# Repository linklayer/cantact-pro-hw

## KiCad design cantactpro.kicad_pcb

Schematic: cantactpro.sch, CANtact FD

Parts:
C1, C2: 4.7u; C_0805; MPN CL21A475KAQNNNG
C3: 10u; C_0805; MPN CL21A106KPFNNNG
C4, C7, C11: 0.1u; C_0603; MPN CC0603ZRY5V9BB104
C5, C6: 470 pF/5 kV; C_1812; MPN 202S43W471KV4E
C8, C9: 0.1u; C_0603; MPN CL10F104ZO8NNNC
C10, C12: 100p; C_0603; MPN 885012206077
D1, D3: LED_GRN; LED_0603; MPN LTST-S270KGKT
D2, D4: LED_RED; LED_0603; MPN LTST-S270KRKT
D5: ESD9X5; SOD-923; MPN ESD9X5.0ST5G
D6: D; D_SMA; MPN S1G
H1, H2, H3, H4: MOUNT_HOLE; MountingHole_3.2mm_M3
J1: USB_B; MPN USB-B1HSB6
J2, J3: DB9; LD09P; MPN LD09P13A4GX00LF
JP1: Boot Switch; TE_1825027-5; MPN 1825027-5
L1: 4.7u; L_0805; MPN LQM21PN4R7NGRD
L2: 47u; L_1206; MPN LB3218T470K
LP1, LP2, LP3, LP4: Light Pipe; SLP3-150-zzz-x; MPN SLP3-150-100-F
R1, R2, R3, R4, R5, R6, R7: 100; R_0603; MPN ESR03EZPJ102
R8: 10k; R_0603; MPN RC0603JR-0710KL
R9, R10: 2.7k; R_0603; MPN RMCF0603JT2K70
R11: 1k; R_0603; MPN RC0603JR-071KL
TP1, TP2, TP3, TP4, TP5, TP6, TP7, TP8, TP9, TP10, TP11, TP12, TP13, TP14, TP15, TP16: TEST; Measurement_Point_Round-TH_Small
U1: TPD2E2U06; SOT-553; MPN TPD2E2U06DRLR
U2: AP2114H-3.3; SOT-223; MPN AP2114H-3.3TRG1
U3: ROE-0505S; MPN ROE-0505S
U4: Si864x; SOIC-16_3.9x9.9mm_Pitch1.27mm; MPN SI8642AB-B-IS1R
U5: LTV-846; SMD-16; MPN LTV-846S
U6, U11: 74LVC1G3157; SOT-363_SC-70-6; MPN SN74LVC1G3157DCKR
U7: NCV7356D1; SOIC-8_3.9x4.9mm_Pitch1.27mm; MPN NCV7356D1R2G
U8: MCP25612FD; SOIC-14_3.9x8.7mm_Pitch1.27mm; MPN MCP25612FD-H/SL
U9, U10: NUP2125; SC-70; MPN NUP2125WTT1G

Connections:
+3V3: C2.1, C4.1, TP3.1, U2.2, U2.4, U4.1, U4.7, U5.3, U5.5, U5.7; also elsewhere on the board
+5VD: C5.1, C7.2, C8.1, C9.1, R9.1, TP9.1, U3.4, U4.10, U4.16, U5.10, U5.12, U5.14, U6.5, U8.3, U8.7, U11.5
+12V: C10.1, C11.2, D6.1 (K), U7.5
/12V_DB9: D6.2 (A), J2.9
/CAN0_MODE: R8.2, TP14.1, U5.9, U6.6, U11.6
/CAN0_RX: TP12.1, U4.12, U11.4
/CAN0_RX_HS: U8.4, U11.3
/CAN0_RX_SW: R9.2, U7.4, U11.1
/CAN0_TX: TP10.1, U4.14, U6.4
/CAN0_TX_HS: U6.3, U8.1
/CAN0_TX_SW: U6.1, U7.1
/CAN1_RX: TP13.1, U4.11, U8.8
/CAN1_TX: TP11.1, U4.13, U8.5
/CANH0: J2.7, U8.13, U10.1
/CANH1: J3.7, U8.10, U9.1
/CANH_SW: C12.2, D5.1 (A1), J2.4, L2.2, R11.1
/CANL0: J2.2, U8.12, U10.2
/CANL1: J3.2, U8.9, U9.2
/MCU/BOOTMODE: JP1.1; also elsewhere on the board
/MCU/CAN0_RX: TP6.1, U4.5; also elsewhere on the board
/MCU/CAN0_TX: TP4.1, U4.3; also elsewhere on the board
/MCU/CAN1_RX: TP7.1, U4.6; also elsewhere on the board
/MCU/CAN1_TX: TP5.1, U4.4; also elsewhere on the board
/MCU/LED_1: D1.2 (A); also elsewhere on the board
/MCU/LED_2: D2.2 (A); also elsewhere on the board
/MCU/LED_3: D3.2 (A); also elsewhere on the board
/MCU/LED_4: D4.2 (A); also elsewhere on the board
/MCU/SWCAN_ENABLE: R7.1; also elsewhere on the board
/MCU/SWCAN_MODE0: R5.1; also elsewhere on the board
/MCU/SWCAN_MODE1: R6.1; also elsewhere on the board
/MCU/USB+: J1.3 (D+), U1.5; also elsewhere on the board
/MCU/USB-: J1.2 (D-), U1.3; also elsewhere on the board
/SW_MODE0: TP15.1, U5.13, U7.2
/SW_MODE1: TP16.1, U5.11, U7.3
GND: C1.2, C2.2, C3.2, C4.2, C6.2, J1.4 (GND), J1.5 (Shield), JP1.2, R1.1, R2.1, R3.1, R4.1, TP2.1, U1.4, U2.1, U3.1, U4.2, U4.8; also elsewhere on the board
GNDD: C6.1, C7.1, C8.2, C9.2, C10.2, C11.1, C12.1, D5.2 (A2), J2.3, J2.6, J3.3, J3.6, R8.1, TP8.1, U3.3, U4.9, U4.15, U6.2, U7.8, U8.2, U8.6, U8.11, U8.14, U9.3, U10.3, U11.2
unnamed: C5.2, L1.2, U3.2
unnamed: D1.1 (K), R1.2
unnamed: D2.1 (K), R2.2
unnamed: D3.1 (K), R3.2
unnamed: D4.1 (K), R4.2
unnamed: L2.1, R10.1, R11.2, U7.7
unnamed: R5.2, U5.4
unnamed: R6.2, U5.6
unnamed: R7.2, U5.8
unnamed: R10.2, U7.6
VBUS: C1.1, C3.1, J1.1 (VBUS), L1.1, TP1.1, U2.3; also elsewhere on the board

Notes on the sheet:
Isolation Barrier
Mounting Holes
Light Pipes

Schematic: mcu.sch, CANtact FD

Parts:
C13, C15, C17, C19, C21, C23, C25, C27, C29: 0.01u; C_0603; MPN C0603C103M5RACTU
C14, C16, C18, C20, C22, C24, C26, C28, C32: 0.1u; C_0603; MPN CL10F104ZO8NNNC
C30, C31: 33p; C_0603; MPN CL10C330JB8NNNC
C33: 4.7u; C_0805; MPN CL21A475KAQNNNG
C34: 10u; C_0805; MPN CL21A106KPFNNNG
J4: SWD; Pin_Header_Straight_2x05_Pitch1.27mm; MPN 3220-10-0100-00
R12: 0; R_0603; MPN RC0603JR-070RL
R13: 12.4k; R_0603; MPN ERJ-3EKF1242V
R14, R15: 10k; R_0603; MPN RC0603JR-0710KL
U12: LPC54616J512BD100; LQFP-100_14x14mm_Pitch0.5mm; MPN LPC54616J512BD100E
Y1: 12 MHz; CSM-3X; MPN ECS-120-20-3X-TR

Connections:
+3V3: C13.1, C14.1, C15.1, C16.1, C17.1, C18.1, C19.1, C20.1, C21.1, C22.1, C23.1, C24.1, C25.1, C26.1, C27.1, C28.1, C29.1, C32.1, C33.1, C34.1, J4.1, R14.2, R15.2, U12.1, U12.10, U12.11, U12.21, U12.31, U12.32, U12.33, U12.45, U12.50, U12.54, U12.75, U12.76, U12.99; also elsewhere on the board
/MCU/BOOTMODE: R12.2, U12.90; also elsewhere on the board
/MCU/CAN0_RX: U12.60; also elsewhere on the board
/MCU/CAN0_TX: U12.58; also elsewhere on the board
/MCU/CAN1_RX: U12.5; also elsewhere on the board
/MCU/CAN1_TX: U12.47; also elsewhere on the board
/MCU/ISP0: U12.87
/MCU/ISP1: R12.1, U12.89
/MCU/LED_1: U12.35; also elsewhere on the board
/MCU/LED_2: U12.36; also elsewhere on the board
/MCU/LED_3: U12.37; also elsewhere on the board
/MCU/LED_4: U12.38; also elsewhere on the board
/MCU/RESETN: J4.10, U12.48
/MCU/SWCAN_ENABLE: U12.77; also elsewhere on the board
/MCU/SWCAN_MODE0: U12.83; also elsewhere on the board
/MCU/SWCAN_MODE1: U12.78; also elsewhere on the board
/MCU/SWCLK: J4.4, R15.1, U12.24
/MCU/SWDIO: J4.2, R14.1, U12.25
/MCU/USB+: U12.13; also elsewhere on the board
/MCU/USB-: U12.12; also elsewhere on the board
GND: C13.2, C14.2, C15.2, C16.2, C17.2, C18.2, C19.2, C20.2, C21.2, C22.2, C23.2, C24.2, C25.2, C26.2, C27.2, C28.2, C29.2, C30.1, C31.1, C32.2, C33.2, C34.2, J4.3, J4.5, J4.9, R13.1, U12.2, U12.6, U12.14, U12.22, U12.30, U12.34, U12.49, U12.51, U12.53, U12.71, U12.79, U12.96; also elsewhere on the board
unnamed: C30.2, U12.20, Y1.2
unnamed: C31.2, U12.19, Y1.1
unnamed: R13.2, U12.7
VBUS: U12.9; also elsewhere on the board

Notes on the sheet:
SWD Debug Interface
DNP R14 for MSC Populate for DFU
TODO: CHECK LOAD CAPS

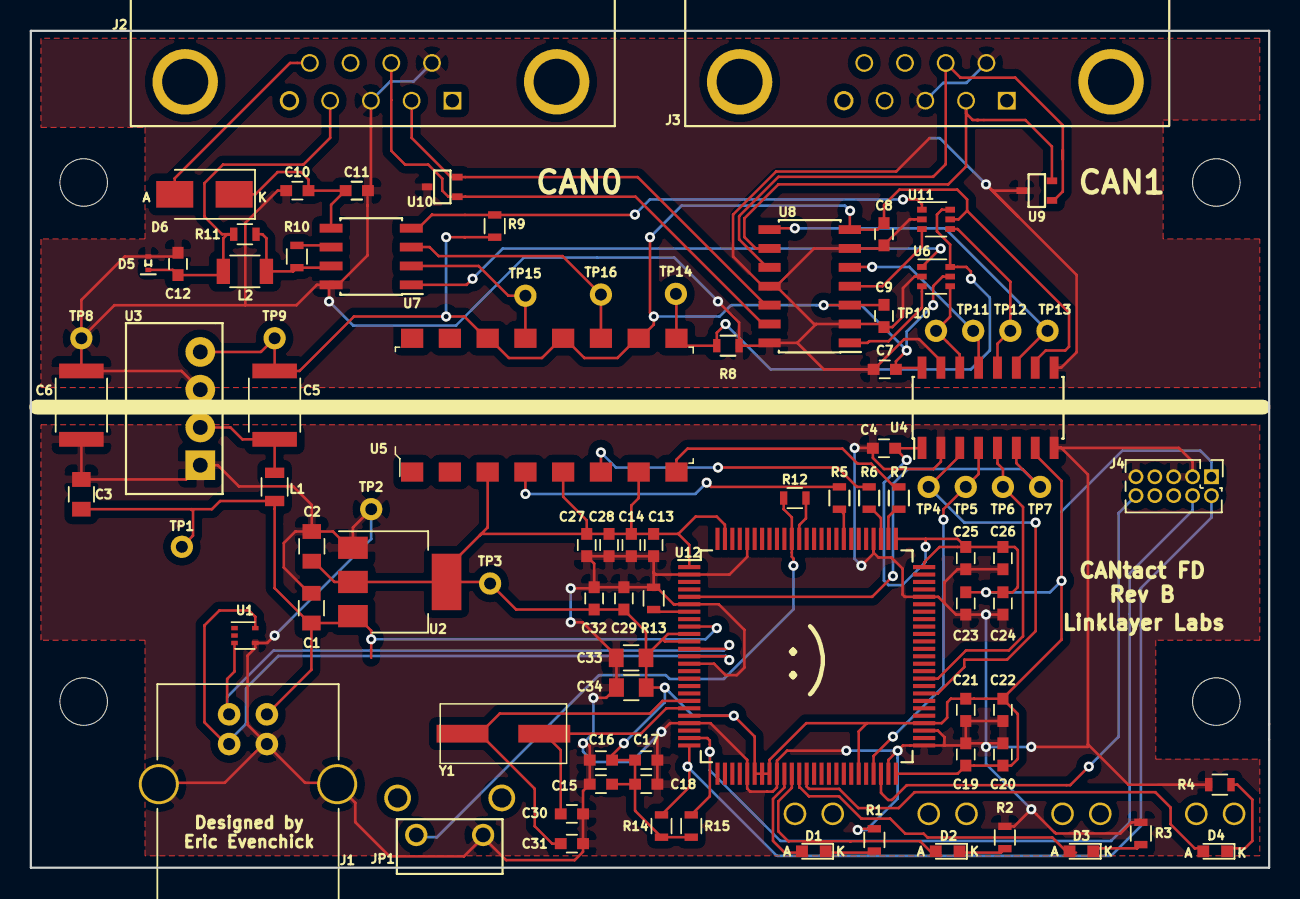
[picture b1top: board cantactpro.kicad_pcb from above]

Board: 2 copper layers, 83.3 x 56.3 mm, 99 parts (0 on the bottom side), 54 nets.

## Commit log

2020-08-20 add license

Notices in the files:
cantactpro.sch:
CC BY-SA 4.0
